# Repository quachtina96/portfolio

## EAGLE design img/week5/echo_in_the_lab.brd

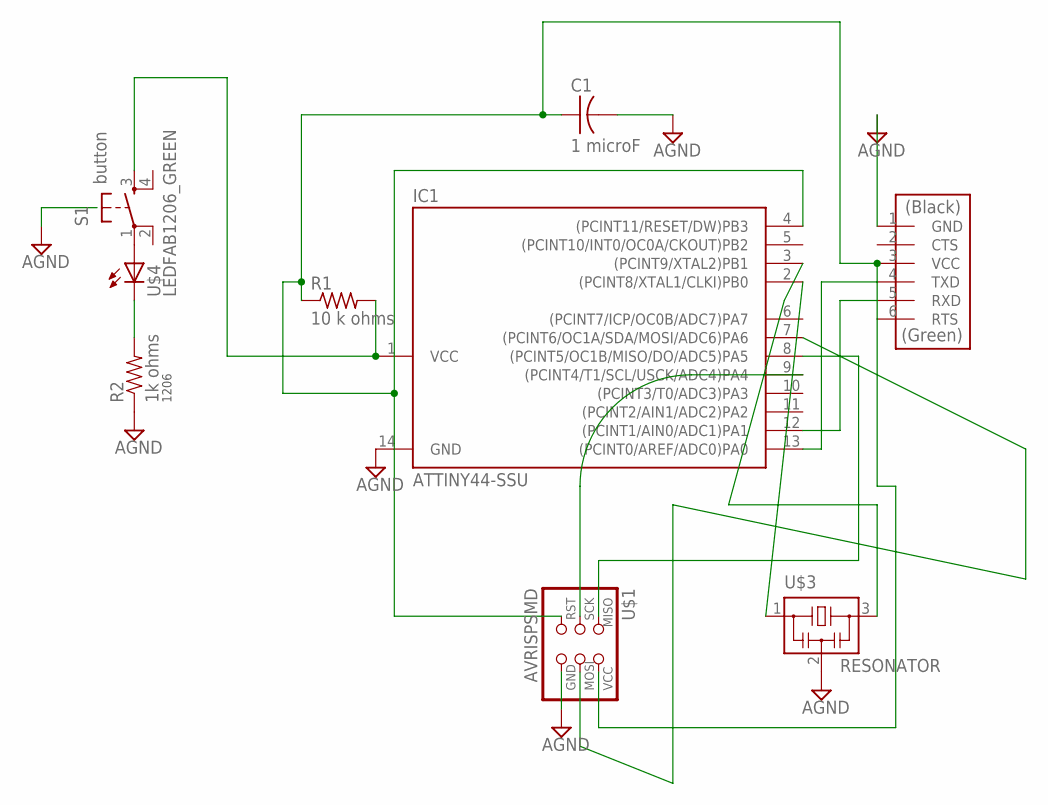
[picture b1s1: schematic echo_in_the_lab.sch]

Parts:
C1: 1 microF; C1206FAB
IC1: ATTINY44-SSU; SOIC14
R1: 10 k ohms; R1206W
R2: 1k ohms; 1206
S1: button; 6MM_SWITCH
U$1: AVRISPSMD; 2X03SMD
U$2: FTDI-SMD-HEADER; 1X06SMD
U$3: RESONATOR; EFOBM
U$4: LEDFAB1206_GREEN; LED1206FAB

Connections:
AGND: C1.2, IC1.14 (GND), R2.1, U$1.6 (GND), U$2.1 (GND), U$3.2
unnamed: IC1.1 (VCC), R1.2, S1.3 (S)
unnamed: R2.2, U$4.2 (C)
unnamed: IC1.13 ((PCINT0/AREF/ADC0)PA0), U$2.4 (TXD)
unnamed: IC1.12 ((PCINT1/AIN0/ADC1)PA1), U$2.5 (RXD)
unnamed: S1.1, U$4.1 (A)
unnamed: IC1.7 ((PCINT6/OC1A/SDA/MOSI/ADC6)PA6), U$1.4 (MOSI)
unnamed: IC1.2 ((PCINT8/XTAL1/CLKI)PB0), U$3.1
unnamed: IC1.3 ((PCINT9/XTAL2)PB1), U$3.3
unnamed: C1.1, IC1.4 ((PCINT11/RESET/DW)PB3), R1.1, U$1.2 (VCC), U$1.5 (RST), U$2.3 (VCC), U$2.6 (RTS)
unnamed: IC1.9 ((PCINT4/T1/SCL/USCK/ADC4)PA4), U$1.3 (SCK)
unnamed: IC1.8 ((PCINT5/OC1B/MISO/DO/ADC5)PA5), U$1.1 (MISO)

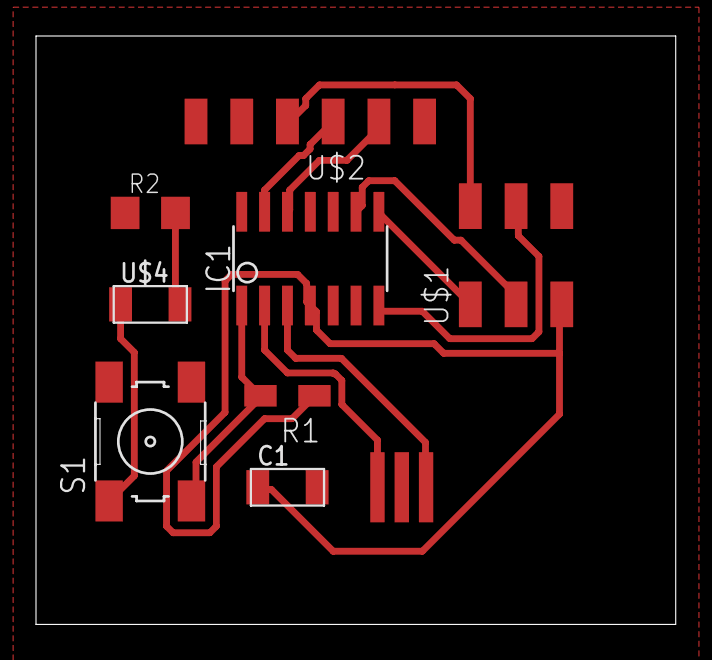
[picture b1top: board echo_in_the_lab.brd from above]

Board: 2 copper layers, 35.5 x 32.7 mm, 9 parts (0 on the bottom side), 12 nets.

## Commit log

2018-09-20 Basis for portfolio website for how to make almost anything
2018-09-26 update week 1,2,3
2018-09-26 use some relative paths and also add basis for week 4 3d blog
2018-09-28 add week 4
2018-10-02 update 3d scan n
2018-10-27 add make something big final images; finish embedded programming doc; add molding and casting blog
